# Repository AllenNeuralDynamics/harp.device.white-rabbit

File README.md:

An RP2040-based 16-output [Harp](https://github.com/harp-tech/protocol)-compliant Clock Synchronizer. 

This device can serve as a drop-in replacement for the [Harp-Tech Clock Synchronizer](https://github.com/harp-tech/device.clocksynchronizer) with added capabilities.

## Features
* 16 output channels for distributing clocks to other devices
* 1 input channel for receiving and synchronizing to another clock source
* 1 Additional Auxiliary Output, providing one of the following at a time:
  * PPS output
  * serial output of the time at user-specifiable baud-rate
* "Used channel detection." Device can identify which channels are in use.

## Ordering ➡ 💸
You can now order V1.0.0 from PCBWay:
* [white-rabbit board](https://www.pcbway.com/project/shareproject/W777629ASS64_W777629ASS46_white_rabbit_v1_0_0_gerbers_1c23dd35.html). Select **PCB + Assembly**

These printed circuit boards are made on-demand.

You will also need:
* [3D Printed Enclosure Walls and Laser Cut Lids](https://cad.onshape.com/documents/e58143a7c9dd2652647e9623/w/90e72faf89a0a2a445ca0911/e/b03806c0bc46a31dc8d5c2c5?renderMode=0&uiState=68af55bb7a7888239c9b7788)
  * right click the component to export each part.

## Auxiliary Output
This device features an auxiliary output that can either produce a *pulse-per-second* (PPS) or UART message at the start of the whole second.
This external signa enables Harp devices to additionally further synchronize with *non*-Harp devices.

### PPS Output
This device optionally outputs a 1[Hz] signal with a 50% duty cycle on the whole second.

Error from the nominal Harp time is < 1[us].

This feature is available on the AUX Port (3-pin terminal block).

### AUX UART Output
This device optionally outputs a the current time in seconds at the start of the whole second.

Error from the nominal Harp time is < 3[us].

This feature is available on the AUX Port (3-pin terminal block), and the baud rate is configurable via Harp Protocol (U32 in Register 36).

## PCBA Enclosure
For the enclosure design, see the companion [OnShape project](https://cad.onshape.com/documents/e58143a7c9dd2652647e9623/w/90e72faf89a0a2a445ca0911/e/b03806c0bc46a31dc8d5c2c5?renderMode=0&uiState=67be1ef78ee27a5b150b11dd).

## Developer Notes
In the firmware's **CMakeLists.txt**, adding (or uncommenting) the debug message below:
````cmake
add_definitions(-DDEBUG)
````
will *override* the Auxiliary port behavior to use the auxiliary uart for `printf`-style debug messages.
`PPS` and `AUX UART` features will not be available in debug mode.

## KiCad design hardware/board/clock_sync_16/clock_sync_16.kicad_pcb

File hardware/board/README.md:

## Overview

These schematic and layout designs have been vetted on prior devices.

High Level Specs:
  * USBC connector (ESD protected with TVS diode).
  * Audio jack connector for Harp synchronization signal (ESD protected with TVS diode).

Component Specs:
  * aqueous washable
  * commonly available components (no end-of-life or last-time-buy)

Layout Specs:
  * 4-layer PCB
      * signal (top), ground, power, signal (bottom)
  * 6-mil traces, 6-mil spacing (0.1524mm)
  * no microvias
  * smallest resistor/capacitor sizes are 0402.
  * Footprints default to "non-hand-soldering"-style.

MCU Schematic Specs:
  * 12MHz oscillator, +/-2.5ppm
  * 16MB flash, Winbond W25Q16JVUXIQ

### USB-Isolated-Only Template Specs
  * Electrically isolated from PC, Analog Devices ADUM4160

## Instructions

Pick a template folder (or none!) as a starting point and delete the remaining other folders.

Rename the folder and all subfolder files of the same name to the name of your project.

Delete the instructions in this file.

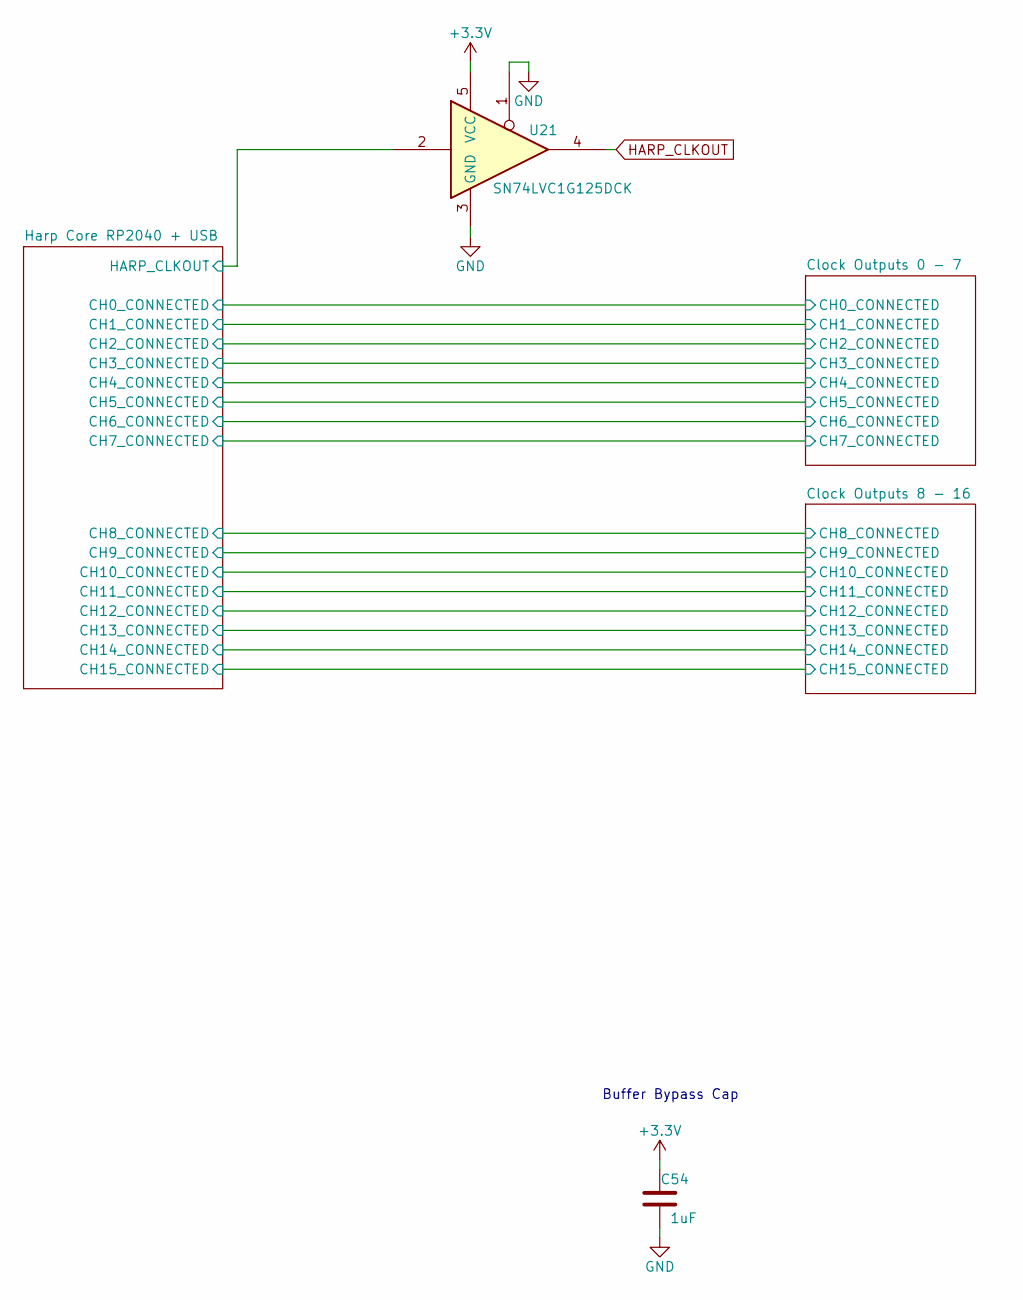
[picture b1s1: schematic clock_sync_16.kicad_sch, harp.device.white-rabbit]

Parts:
C54: 1uF; C_0402_1005Metric; Rated Voltage 35V
U21: SN74LVC1G125DCK; Texas_R-PDSO-G5_DCK-5

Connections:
+3.3V: C54.1, U21.5 (VCC); also elsewhere on the board
/Harp Core RP2040 + USB/HARP_CLKOUT: U21.2; also elsewhere on the board
GND: C54.2, U21.1, U21.3 (GND); also elsewhere on the board
HARP_CLKOUT: U21.4; also elsewhere on the board

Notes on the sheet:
Buffer Bypass Cap

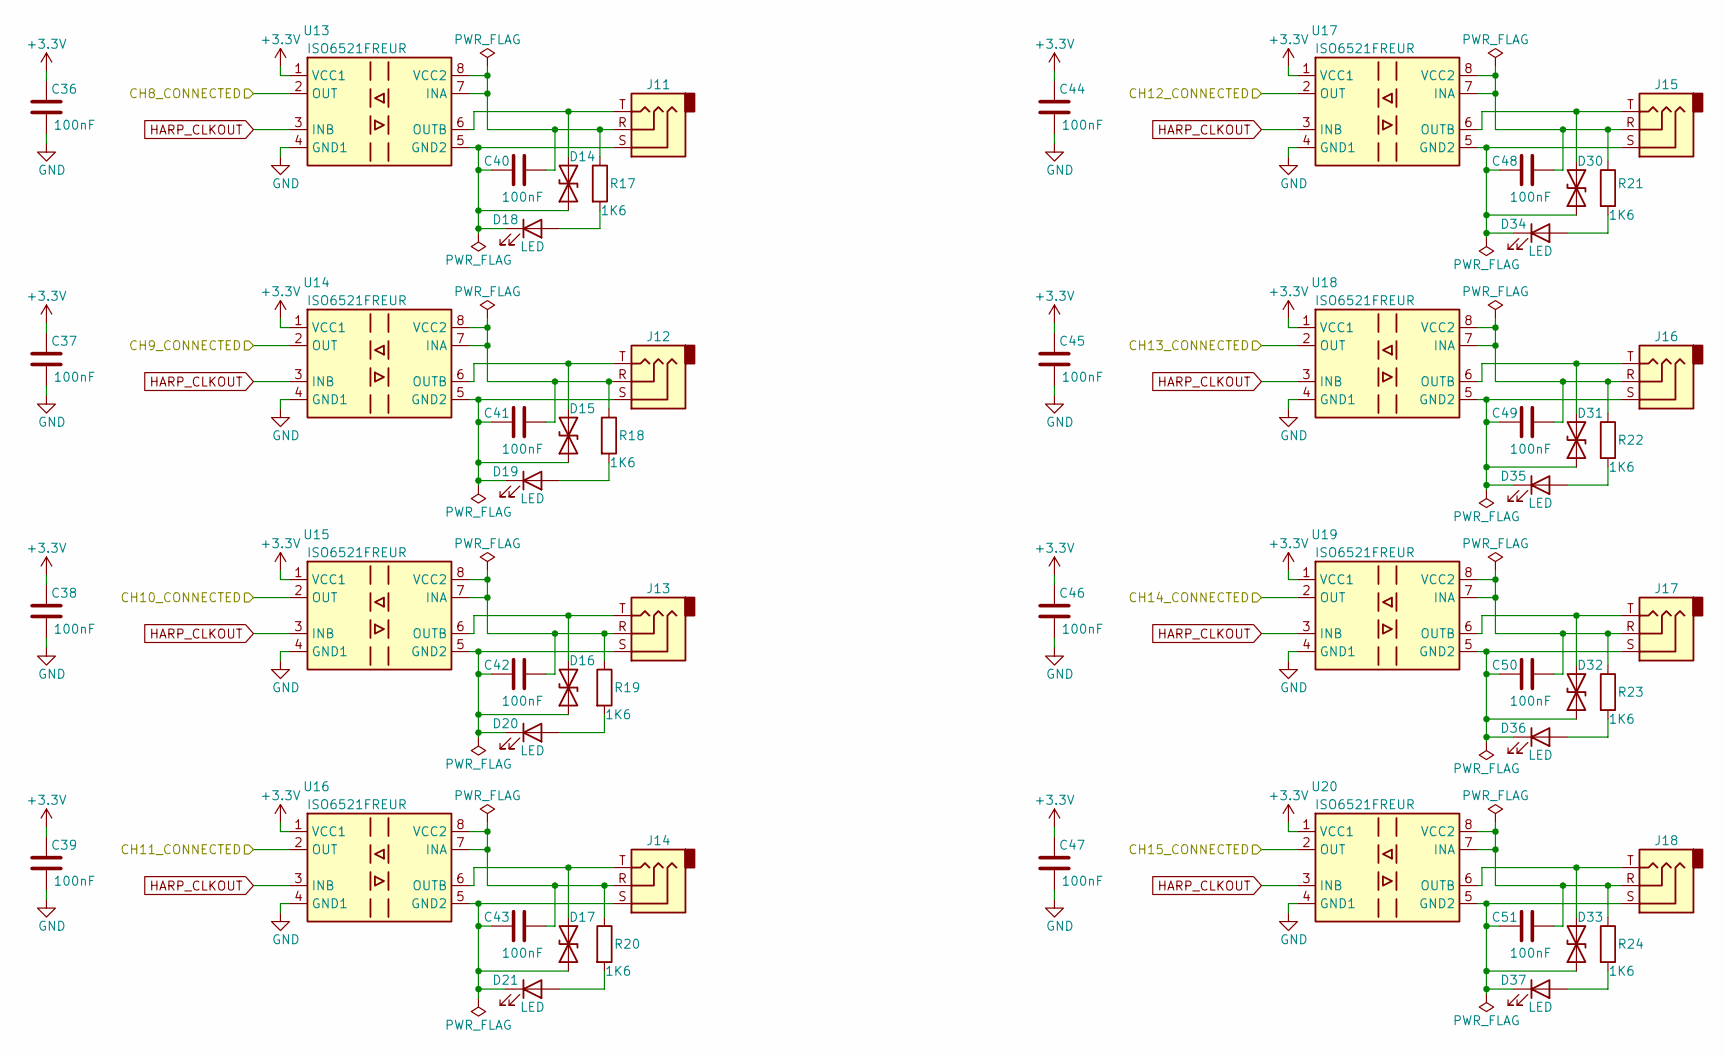
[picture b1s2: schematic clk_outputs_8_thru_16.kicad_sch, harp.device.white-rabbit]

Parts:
C36, C37, C38, C39, C40, C41, C42, C43, C44, C45, C46, C47, C48, C49, C50, C51: 100nF; C_0402_1005Metric; Rated Voltage 16V; Tolerance 10%
D14, D15, D16, D17, D30, D31, D32, D33: D_TVS; D_0402_1005Metric
D18, D19, D20, D21, D34, D35, D36, D37: LED; LED_0603_1608Metric_Pad1.05x0.95mm_HandSolder
J11, J12, J13, J14, J15, J16, J17, J18: AudioJack3; Jack_3.5mm_Kycon_STX-3680-5NB_Vertical
R17, R18, R19, R20, R21, R22, R23, R24: 1K6; R_0402_1005Metric
U13, U14, U15, U16, U17, U18, U19, U20: ISO6521FREUR; DFN-8_3x2mm_P0.5mm

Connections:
+3.3V: C36.2, C37.2, C38.2, C39.2, C44.2, C45.2, C46.2, C47.2, U13.1 (VCC1), U14.1 (VCC1), U15.1 (VCC1), U16.1 (VCC1), U17.1 (VCC1), U18.1 (VCC1), U19.1 (VCC1), U20.1 (VCC1); also elsewhere on the board
/Clock Outputs 8 - 16/CH8_CONNECTED: U13.2 (OUT); also elsewhere on the board
/Clock Outputs 8 - 16/CH9_CONNECTED: U14.2 (OUT); also elsewhere on the board
/Clock Outputs 8 - 16/CH10_CONNECTED: U15.2 (OUT); also elsewhere on the board
/Clock Outputs 8 - 16/CH11_CONNECTED: U16.2 (OUT); also elsewhere on the board
/Clock Outputs 8 - 16/CH12_CONNECTED: U17.2 (OUT); also elsewhere on the board
/Clock Outputs 8 - 16/CH13_CONNECTED: U18.2 (OUT); also elsewhere on the board
/Clock Outputs 8 - 16/CH14_CONNECTED: U19.2 (OUT); also elsewhere on the board
/Clock Outputs 8 - 16/CH15_CONNECTED: U20.2 (OUT); also elsewhere on the board
GND: C36.1, C37.1, C38.1, C39.1, C44.1, C45.1, C46.1, C47.1, U13.4 (GND1), U14.4 (GND1), U15.4 (GND1), U16.4 (GND1), U17.4 (GND1), U18.4 (GND1), U19.4 (GND1), U20.4 (GND1); also elsewhere on the board
HARP_CLKOUT: U13.3 (INB), U14.3 (INB), U15.3 (INB), U16.3 (INB), U17.3 (INB), U18.3 (INB), U19.3 (INB), U20.3 (INB); also elsewhere on the board
unnamed: C40.2, D14.1 (A1), D18.1 (K), J11.S, U13.5 (GND2)
unnamed: D14.2 (A2), J11.T, U13.6 (OUTB)
unnamed: C41.2, D15.1 (A1), D19.1 (K), J12.S, U14.5 (GND2)
unnamed: D15.2 (A2), J12.T, U14.6 (OUTB)
unnamed: C42.2, D16.1 (A1), D20.1 (K), J13.S, U15.5 (GND2)
unnamed: D16.2 (A2), J13.T, U15.6 (OUTB)
unnamed: C43.2, D17.1 (A1), D21.1 (K), J14.S, U16.5 (GND2)
unnamed: D17.2 (A2), J14.T, U16.6 (OUTB)
unnamed: D18.2 (A), R17.2
unnamed: D19.2 (A), R18.2
unnamed: D20.2 (A), R19.2
unnamed: D21.2 (A), R20.2
unnamed: C48.2, D30.1 (A1), D34.1 (K), J15.S, U17.5 (GND2)
unnamed: D30.2 (A2), J15.T, U17.6 (OUTB)
unnamed: C49.2, D31.1 (A1), D35.1 (K), J16.S, U18.5 (GND2)
unnamed: D31.2 (A2), J16.T, U18.6 (OUTB)
unnamed: C50.2, D32.1 (A1), D36.1 (K), J17.S, U19.5 (GND2)
unnamed: D32.2 (A2), J17.T, U19.6 (OUTB)
unnamed: C51.2, D33.1 (A1), D37.1 (K), J18.S, U20.5 (GND2)
unnamed: D33.2 (A2), J18.T, U20.6 (OUTB)
unnamed: D34.2 (A), R21.2
unnamed: D35.2 (A), R22.2
unnamed: D36.2 (A), R23.2
unnamed: D37.2 (A), R24.2
unnamed: C40.1, J11.R, R17.1, U13.7 (INA), U13.8 (VCC2)
unnamed: C41.1, J12.R, R18.1, U14.7 (INA), U14.8 (VCC2)
unnamed: C42.1, J13.R, R19.1, U15.7 (INA), U15.8 (VCC2)
unnamed: C43.1, J14.R, R20.1, U16.7 (INA), U16.8 (VCC2)
unnamed: C48.1, J15.R, R21.1, U17.7 (INA), U17.8 (VCC2)
unnamed: C49.1, J16.R, R22.1, U18.7 (INA), U18.8 (VCC2)
unnamed: C50.1, J17.R, R23.1, U19.7 (INA), U19.8 (VCC2)
unnamed: C51.1, J18.R, R24.1, U20.7 (INA), U20.8 (VCC2)

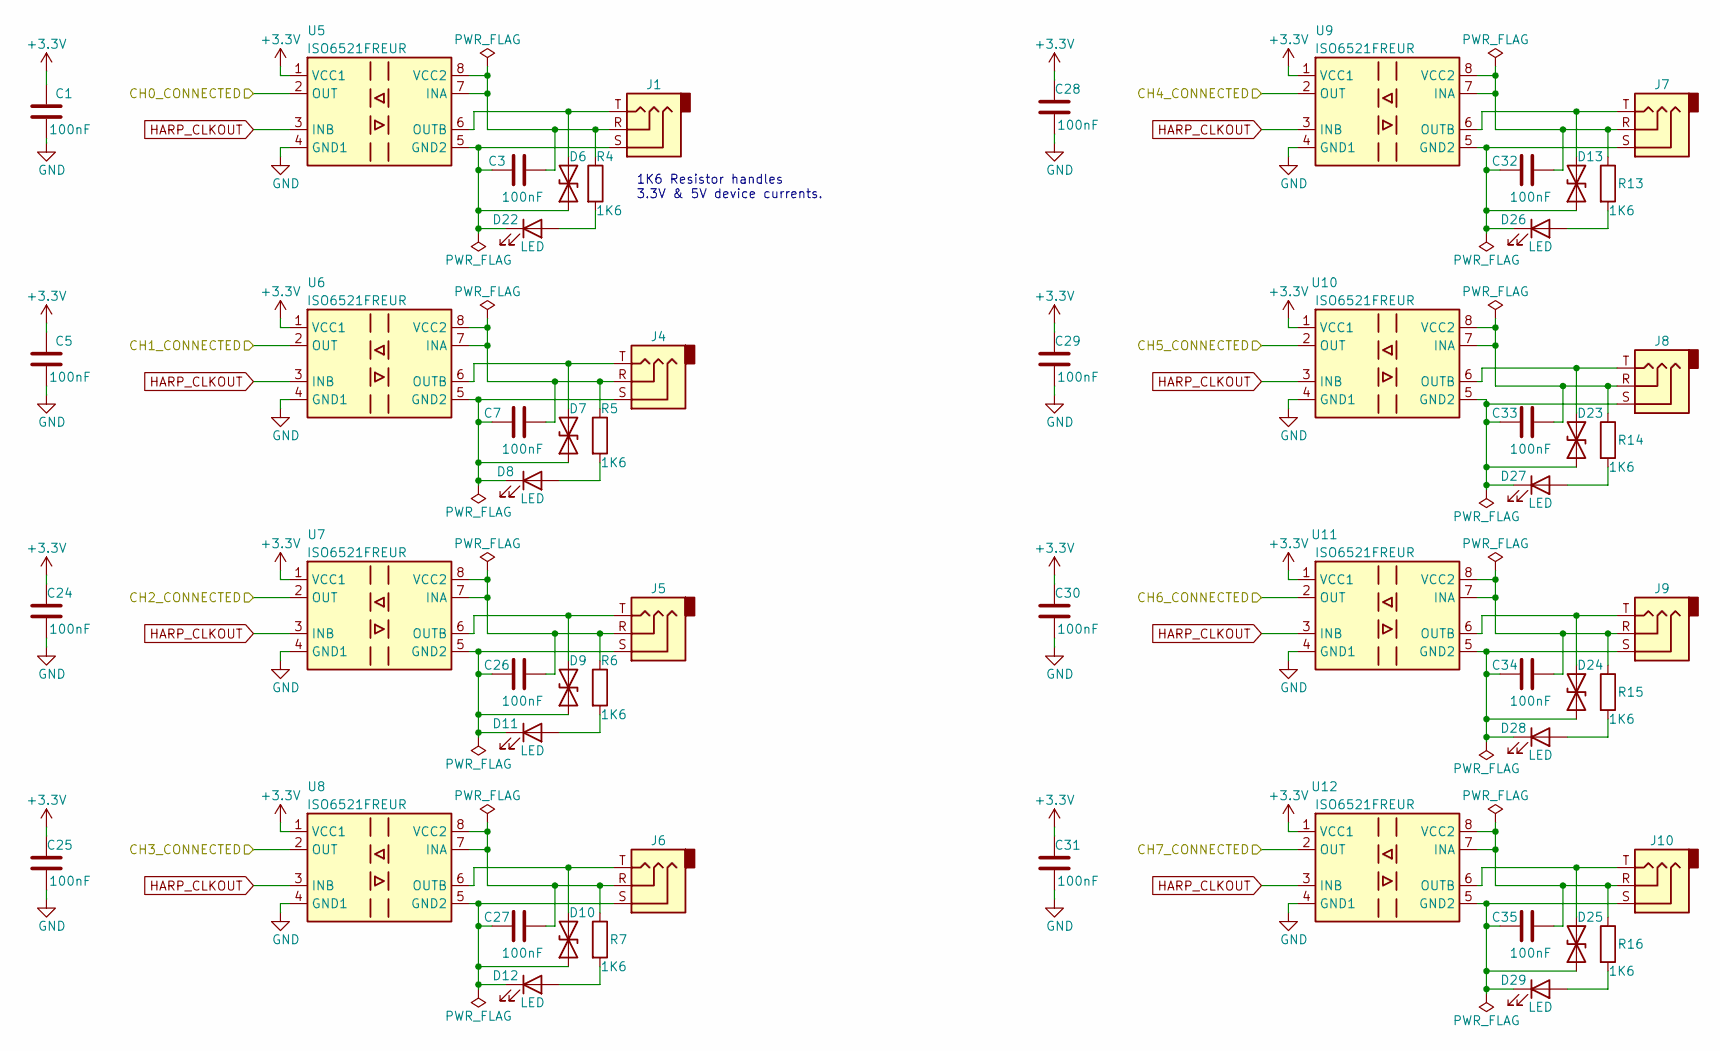
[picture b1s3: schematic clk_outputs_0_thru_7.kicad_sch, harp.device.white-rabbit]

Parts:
C1, C3, C5, C7, C24, C25, C26, C27, C28, C29, C30, C31, C32, C33, C34, C35: 100nF; C_0402_1005Metric; Rated Voltage 16V; Tolerance 10%
D6, D7, D9, D10, D13, D23, D24, D25: D_TVS; D_0402_1005Metric
D8, D11, D12, D22, D26, D27, D28, D29: LED; LED_0603_1608Metric_Pad1.05x0.95mm_HandSolder
J1, J4, J5, J6, J7, J8, J9, J10: AudioJack3; Jack_3.5mm_Kycon_STX-3680-5NB_Vertical
R4, R5, R6, R7, R13, R14, R15, R16: 1K6; R_0402_1005Metric
U5, U6, U7, U8, U9, U10, U11, U12: ISO6521FREUR; DFN-8_3x2mm_P0.5mm

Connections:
+3.3V: C1.2, C5.2, C24.2, C25.2, C28.2, C29.2, C30.2, C31.2, U5.1 (VCC1), U6.1 (VCC1), U7.1 (VCC1), U8.1 (VCC1), U9.1 (VCC1), U10.1 (VCC1), U11.1 (VCC1), U12.1 (VCC1); also elsewhere on the board
/Clock Outputs 0 - 7/CH0_CONNECTED: U5.2 (OUT); also elsewhere on the board
/Clock Outputs 0 - 7/CH1_CONNECTED: U6.2 (OUT); also elsewhere on the board
/Clock Outputs 0 - 7/CH2_CONNECTED: U7.2 (OUT); also elsewhere on the board
/Clock Outputs 0 - 7/CH3_CONNECTED: U8.2 (OUT); also elsewhere on the board
/Clock Outputs 0 - 7/CH4_CONNECTED: U9.2 (OUT); also elsewhere on the board
/Clock Outputs 0 - 7/CH5_CONNECTED: U10.2 (OUT); also elsewhere on the board
/Clock Outputs 0 - 7/CH6_CONNECTED: U11.2 (OUT); also elsewhere on the board
/Clock Outputs 0 - 7/CH7_CONNECTED: U12.2 (OUT); also elsewhere on the board
GND: C1.1, C5.1, C24.1, C25.1, C28.1, C29.1, C30.1, C31.1, U5.4 (GND1), U6.4 (GND1), U7.4 (GND1), U8.4 (GND1), U9.4 (GND1), U10.4 (GND1), U11.4 (GND1), U12.4 (GND1); also elsewhere on the board
HARP_CLKOUT: U5.3 (INB), U6.3 (INB), U7.3 (INB), U8.3 (INB), U9.3 (INB), U10.3 (INB), U11.3 (INB), U12.3 (INB); also elsewhere on the board
unnamed: D6.2 (A2), J1.T, U5.6 (OUTB)
unnamed: C7.2, D7.1 (A1), D8.1 (K), J4.S, U6.5 (GND2)
unnamed: D7.2 (A2), J4.T, U6.6 (OUTB)
unnamed: D8.2 (A), R5.2
unnamed: D9.2 (A2), J5.T, U7.6 (OUTB)
unnamed: C27.2, D10.1 (A1), D12.1 (K), J6.S, U8.5 (GND2)
unnamed: D10.2 (A2), J6.T, U8.6 (OUTB)
unnamed: D11.2 (A), R6.2
unnamed: C26.2, D9.1 (A1), D11.1 (K), J5.S, U7.5 (GND2)
unnamed: D12.2 (A), R7.2
unnamed: C32.2, D13.1 (A1), D26.1 (K), J7.S, U9.5 (GND2)
unnamed: D13.2 (A2), J7.T, U9.6 (OUTB)
unnamed: D22.2 (A), R4.2
unnamed: C3.2, D6.1 (A1), D22.1 (K), J1.S, U5.5 (GND2)
unnamed: C33.2, D23.1 (A1), D27.1 (K), J8.S, U10.5 (GND2)
unnamed: D23.2 (A2), J8.T, U10.6 (OUTB)
unnamed: C34.2, D24.1 (A1), D28.1 (K), J9.S, U11.5 (GND2)
unnamed: D24.2 (A2), J9.T, U11.6 (OUTB)
unnamed: C35.2, D25.1 (A1), D29.1 (K), J10.S, U12.5 (GND2)
unnamed: D25.2 (A2), J10.T, U12.6 (OUTB)
unnamed: D26.2 (A), R13.2
unnamed: D27.2 (A), R14.2
unnamed: D28.2 (A), R15.2
unnamed: D29.2 (A), R16.2
unnamed: C3.1, J1.R, R4.1, U5.7 (INA), U5.8 (VCC2)
unnamed: C7.1, J4.R, R5.1, U6.7 (INA), U6.8 (VCC2)
unnamed: C26.1, J5.R, R6.1, U7.7 (INA), U7.8 (VCC2)
unnamed: C27.1, J6.R, R7.1, U8.7 (INA), U8.8 (VCC2)
unnamed: C32.1, J7.R, R13.1, U9.7 (INA), U9.8 (VCC2)
unnamed: C33.1, J8.R, R14.1, U10.7 (INA), U10.8 (VCC2)
unnamed: C34.1, J9.R, R15.1, U11.7 (INA), U11.8 (VCC2)
unnamed: C35.1, J10.R, R16.1, U12.7 (INA), U12.8 (VCC2)

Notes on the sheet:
1K6 Resistor handles 3.3V & 5V device currents.

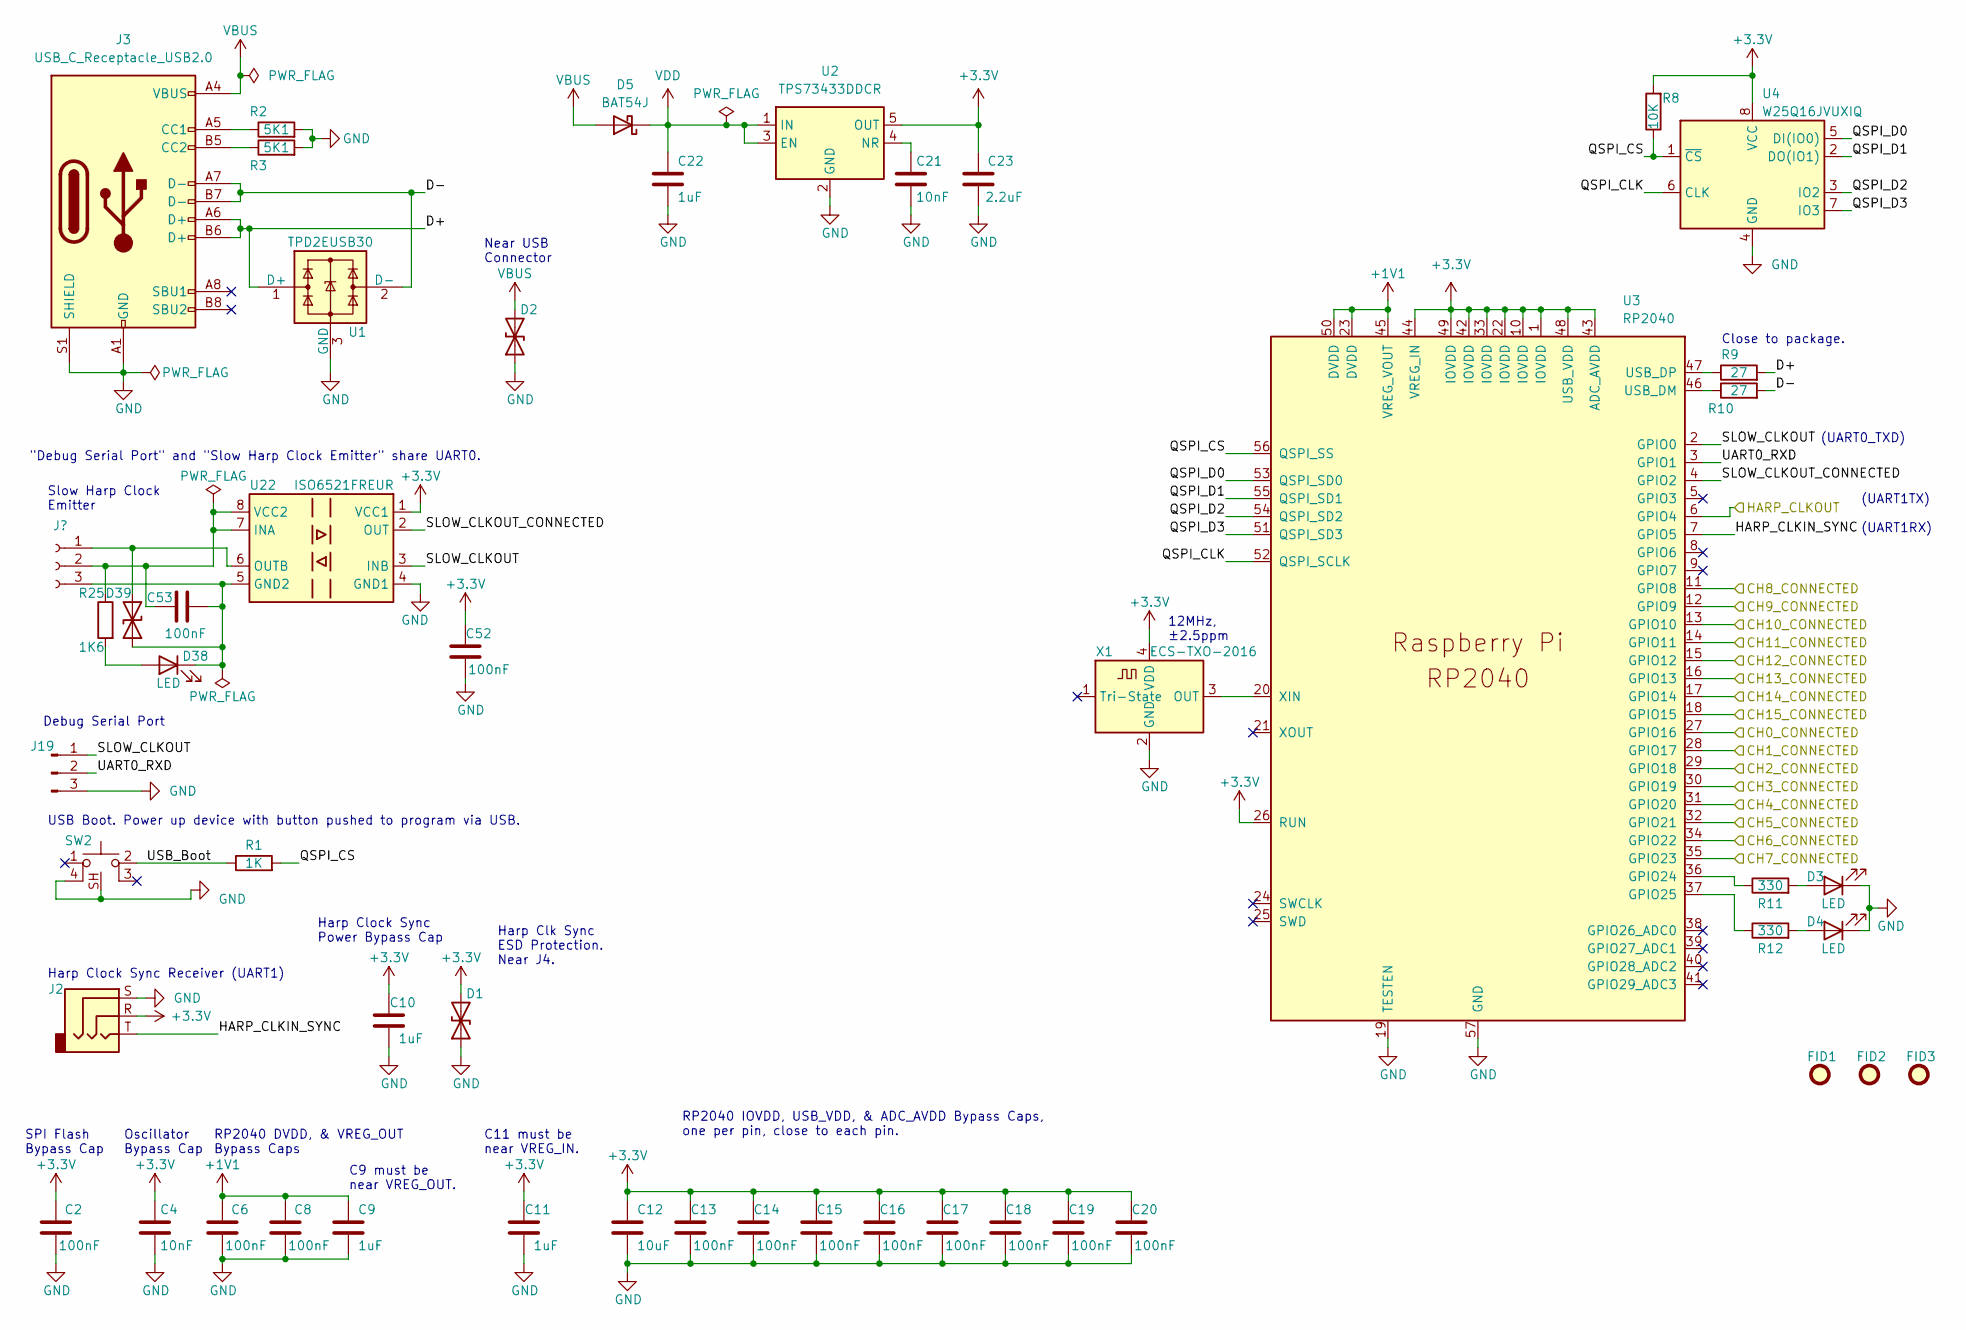
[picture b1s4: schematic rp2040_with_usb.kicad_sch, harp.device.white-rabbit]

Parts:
C2, C6, C8, C13, C14, C15, C16, C17, C18, C19, C20, C52, C53: 100nF; C_0402_1005Metric; Rated Voltage 16V; Tolerance 10%
C4, C21: 10nF; C_0402_1005Metric; Rated Voltage 25V; Tolerance 2%
C9, C10, C11, C22: 1uF; C_0402_1005Metric; Rated Voltage 35V
C12: 10uF; C_0805_2012Metric; Rated Voltage 25V
C23: 2.2uF; C_0402_1005Metric; Rated Voltage 10V
D1, D2, D39: D_TVS; D_0402_1005Metric
D3, D4, D38: LED; LED_0603_1608Metric_Pad1.05x0.95mm_HandSolder
D5: BAT54J; D_SOD-323F
FID1, FID2, FID3: Fiducial; Fiducial_0.5mm_Mask1mm
J1: Conn_01x03_Female; PhoenixContact_MCV_1,5_3-G-3.5_1x03_P3.50mm_Vertical
J2: AudioJack3; Jack_3.5mm_CUI_SJ-3524-SMT_Horizontal
J3: USB_C_Receptacle_USB2.0; USB_C_Receptacle_JAE_DX07S016JA1R1500
J19: Conn_01x03_Male; PinHeader_1x03_P2.54mm_Vertical
R1: 1K; R_0402_1005Metric; Tolerance 1%
R2, R3: 5K1; R_0402_1005Metric; Tolerance 1%
R8: 10K; R_0402_1005Metric; Tolerance 1%
R9, R10: 27; R_0402_1005Metric; Tolerance 1%
R11, R12: 330; R_0402_1005Metric; Tolerance 0.1%
R25: 1K6; R_0402_1005Metric
SW2: SW_Push_1P1T-SH_NO_Vertical_Wuerth_WS-TASV
U1: TPD2EUSB30; Texas_DRT-3
U2: TPS73433DDCR; SOT-23-5
U3: RP2040; RP2040-QFN-56
U4: W25Q16JVUXIQ; Winbond-8USON-2x3mm
U22: ISO6521FREUR; DFN-8_3x2mm_P0.5mm
X1: ECS-TXO-2016; Crystal_SMD_2016-4Pin_2.0x1.6mm; Tolerance ±2.5ppm

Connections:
+1V1: C6.2, C8.2, C9.1, U3.23 (DVDD), U3.45 (VREG_VOUT), U3.50 (DVDD)
+3.3V: C2.2, C4.1, C10.1, C11.1, C12.1, C13.2, C14.2, C15.2, C16.2, C17.2, C18.2, C19.2, C20.2, C23.2, C52.2, D1.2 (A2), J2.R, R8.2, U2.5 (OUT), U3.1 (IOVDD), U3.10 (IOVDD), U3.22 (IOVDD), U3.26 (RUN), U3.33 (IOVDD), U3.42 (IOVDD), U3.43 (ADC_AVDD), U3.44 (VREG_IN), U3.48 (USB_VDD), U3.49 (IOVDD), U4.8 (VCC), U22.1 (VCC1), X1.4 (VDD); also elsewhere on the board
/Clock Outputs 0 - 7/CH0_CONNECTED: U3.27 (GPIO16); also elsewhere on the board
/Clock Outputs 0 - 7/CH1_CONNECTED: U3.28 (GPIO17); also elsewhere on the board
/Clock Outputs 0 - 7/CH2_CONNECTED: U3.29 (GPIO18); also elsewhere on the board
/Clock Outputs 0 - 7/CH3_CONNECTED: U3.30 (GPIO19); also elsewhere on the board
/Clock Outputs 0 - 7/CH4_CONNECTED: U3.31 (GPIO20); also elsewhere on the board
/Clock Outputs 0 - 7/CH5_CONNECTED: U3.32 (GPIO21); also elsewhere on the board
/Clock Outputs 0 - 7/CH6_CONNECTED: U3.34 (GPIO22); also elsewhere on the board
/Clock Outputs 0 - 7/CH7_CONNECTED: U3.35 (GPIO23); also elsewhere on the board
/Clock Outputs 8 - 16/CH8_CONNECTED: U3.11 (GPIO8); also elsewhere on the board
/Clock Outputs 8 - 16/CH9_CONNECTED: U3.12 (GPIO9); also elsewhere on the board
/Clock Outputs 8 - 16/CH10_CONNECTED: U3.13 (GPIO10); also elsewhere on the board
/Clock Outputs 8 - 16/CH11_CONNECTED: U3.14 (GPIO11); also elsewhere on the board
/Clock Outputs 8 - 16/CH12_CONNECTED: U3.15 (GPIO12); also elsewhere on the board
/Clock Outputs 8 - 16/CH13_CONNECTED: U3.16 (GPIO13); also elsewhere on the board
/Clock Outputs 8 - 16/CH14_CONNECTED: U3.17 (GPIO14); also elsewhere on the board
/Clock Outputs 8 - 16/CH15_CONNECTED: U3.18 (GPIO15); also elsewhere on the board
/Harp Core RP2040 + USB/D+: J3.A6 (D+), J3.B6 (D+), R9.2, U1.1 (D+)
/Harp Core RP2040 + USB/D-: J3.A7 (D-), J3.B7 (D-), R10.2, U1.2 (D-)
/Harp Core RP2040 + USB/HARP_CLKIN_SYNC: J2.T, U3.7 (GPIO5)
/Harp Core RP2040 + USB/HARP_CLKOUT: U3.6 (GPIO4); also elsewhere on the board
/Harp Core RP2040 + USB/QSPI_CLK: U3.52 (QSPI_SCLK), U4.6 (CLK)
/Harp Core RP2040 + USB/QSPI_CS: R1.2, R8.1, U3.56 (QSPI_SS), U4.1 (~CS)
/Harp Core RP2040 + USB/QSPI_D0: U3.53 (QSPI_SD0), U4.5 (DI(IO0))
/Harp Core RP2040 + USB/QSPI_D1: U3.55 (QSPI_SD1), U4.2 (DO(IO1))
/Harp Core RP2040 + USB/QSPI_D2: U3.54 (QSPI_SD2), U4.3 (IO2)
/Harp Core RP2040 + USB/QSPI_D3: U3.51 (QSPI_SD3), U4.7 (IO3)
/Harp Core RP2040 + USB/SLOW_CLKOUT: J19.1, U3.2 (GPIO0), U22.3 (INB)
/Harp Core RP2040 + USB/SLOW_CLKOUT_CONNECTED: U3.4 (GPIO2), U22.2 (OUT)
/Harp Core RP2040 + USB/UART0_RXD: J19.2, U3.3 (GPIO1)
/Harp Core RP2040 + USB/USB_Boot: R1.1, SW2.2
GND: C2.1, C4.2, C6.1, C8.1, C9.2, C10.2, C11.2, C12.2, C13.1, C14.1, C15.1, C16.1, C17.1, C18.1, C19.1, C20.1, C21.2, C22.2, C23.1, C52.1, D1.1 (A1), D2.1 (A1), D3.1 (K), D4.1 (K), J2.S, J3.A1 (GND), J3.A12 (GND), J3.B1 (GND), J3.B12 (GND), J3.S1 (SHIELD), J19.3, R2.2, R3.2, SW2.4, SW2.SH, U1.3 (GND), U2.2 (GND), U3.19 (TESTEN), U3.57 (GND), U4.4 (GND), U22.4 (GND1), X1.2 (GND); also elsewhere on the board
unnamed: D3.2 (A), R11.2
unnamed: D4.2 (A), R12.2
unnamed: D38.2 (A), R25.2
unnamed: J3.A5 (CC1), R2.1
unnamed: J3.B5 (CC2), R3.1
unnamed: C21.1, U2.4 (NR)
unnamed: R11.1, U3.36 (GPIO24)
unnamed: R12.1, U3.37 (GPIO25)
unnamed: R10.1, U3.46 (USB_DM)
unnamed: R9.1, U3.47 (USB_DP)
unnamed: U3.20 (XIN), X1.3 (OUT)
VBUS: D2.2 (A2), D5.2 (A), J3.A4 (VBUS), J3.A9 (VBUS), J3.B4 (VBUS), J3.B9 (VBUS)
VDD: C22.1, D5.1 (K), U2.1 (IN), U2.3 (EN)

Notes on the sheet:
C11 must be near VREG_IN.
"Debug Serial Port" and "Slow Harp Clock Emitter" share UART0.
C9 must be near VREG_OUT.
SPI Flash Bypass Cap
Close to package.
Harp Clock Sync Power Bypass Cap
Harp Clock Sync Receiver (UART1)
Oscillator Bypass Cap
RP2040 DVDD, & VREG_OUT Bypass Caps
Debug Serial Port
USB Boot. Power up device with button pushed to program via USB.
(UART0_TXD)
(UART1TX) (UART1RX)
RP2040 IOVDD, USB_VDD, & ADC_AVDD Bypass Caps, one per pin, close to each pin.
Near USB Connector
Slow Harp Clock Emitter
12MHz, ±2.5ppm
Harp Clk Sync ESD Protection. Near J4.

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
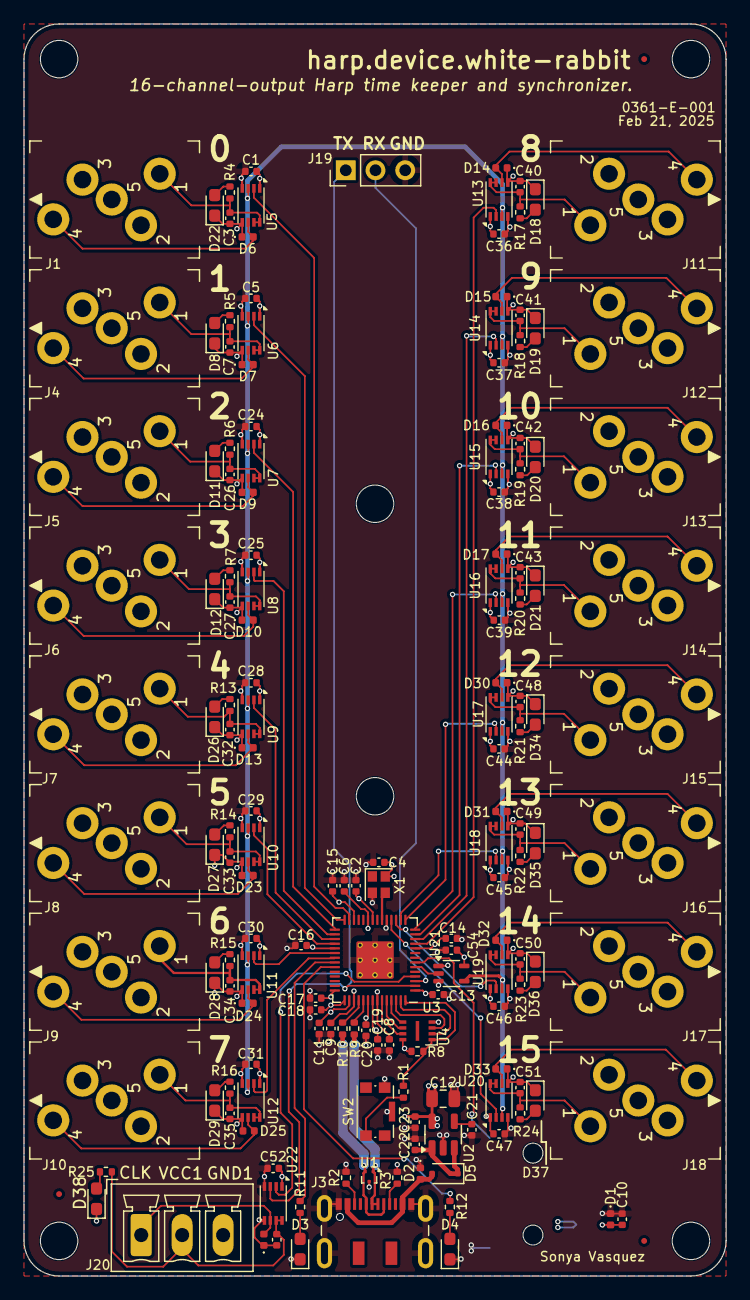
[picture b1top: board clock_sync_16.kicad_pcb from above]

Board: 4 copper layers, 60.0 x 107.0 mm, 165 parts (1 on the bottom side), 114 nets.

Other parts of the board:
J20: Conn_01x03_Female; PhoenixContact_MCV_1,5_3-G-3.5_1x03_P3.50mm_Vertical

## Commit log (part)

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2024-05-20 draft schematic
2024-05-30 route pcb v0.1
2024-05-31 draft v0.1 pcb
2024-06-21 draft firmware
2024-07-15 draft firmware to emit clock msg
2024-07-16 dispatch works
2024-07-18 add basic register functionality
2024-07-18 draft ConnectedDevices behavior
2024-07-18 add timer msg example
2024-07-18 add read-connected-devices demo
2024-07-18 draft slow clk sync functionality
2024-07-23 add 3d model as step
2024-07-23 add short git hash to CMakeLists.txt
2024-07-23 add enclosure
2024-07-25 Add interface generator
2024-07-25 Add draft of device.yml
2024-07-25 Add first interface
2024-07-30 Include missing License and Icon assets
2024-07-30 Normalize directory to other aind harp device packages
2024-08-23 update case
2024-08-23 update enclosure
2024-09-04 add pps/slow_uart output options
2024-09-04 add pps
2024-09-07 update setup order
2024-09-09 add aux uart baud rate
2024-09-09 fix aux baud rate off-by-1
2024-09-09 add enable aux uart example
2024-09-10 fix off-by-1s error
2024-09-10 bugfix time offset
2024-09-11 Expose Auxiliary port baud rate register (36) to bonsai interface
2024-09-11 Bump package version
2024-09-11 add img
2024-09-11 add supplementary timing diagrams
2024-09-12 Hint baud rate limits in device schema
2024-09-12 Regenerate interface
2024-09-12 Update README.md
    Add reference names to readme
2024-09-12 clamp max baud rate
2024-09-12 Bump firmware device in schema
2024-09-12 Update hardware targets in device schema
2024-09-12 update harp core
2024-09-16 refactor to updated harp core
2024-09-18 implement software-based aux uart
2024-11-08 Update bonsai generators
2024-11-09 Fix schema source
2025-01-24 update harp core & uart lib
2025-02-21 update harp core; update led resistors and deprecated parts; bump versions
2025-02-21 update missing BOM field
